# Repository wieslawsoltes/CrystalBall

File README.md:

# CrystalBall

**Aether Orb — hardware, firmware, manufacturing engineering and a WebGPU digital studio.**

A tabletop AI-assisted entertainment prop with a hollow optical globe, an operator-facing reflected display, push-to-talk audio and a decorative illuminated base. The browser recreates the concept's sphere, purple illumination, black/gold celestial base and private teller display; the Engineering view loads the actual CAD tessellation.

**Release: engineering candidate. Not approved for production manufacture or sale.** Physical fit, optical privacy/readability, supplier selection, thermal/electrical qualification, production security and market compliance remain release gates. The browser's volumetric nebula is artistic, not a claim that LEDs create a cloud inside an empty globe. Exact visual identity has not been accepted.

## Browser prototype online

**[Open CrystalBall on GitHub Pages](https://wieslawsoltes.github.io/CrystalBall/)** — offline demo by default, including the WebGPU experience and CAD inspector. The Python gateway is hosted separately. [Pages deployment and pairing](docs/github-pages.md) explains the repository-path checks, publication manifest and CORS configuration.

## Rendering and input hardening

The renderer now caps surface area and adapter dimensions, allows only one outstanding GPU frame, suspends redundant paused/CAD submissions, and adapts resolution with hysteresis. Device loss/disposal releases GPU resources and aborts stale initialization or CAD uploads. Two-finger pinch, focused-canvas arrow keys, +/- zoom and Home reset complement mouse controls. See [resource ownership and validation](docs/renderer-lifecycle.md). These are bounded-work/resource improvements, not measured hardware FPS claims.

## Start the browser without an API key

```sh
git clone https://github.com/wieslawsoltes/CrystalBall.git
cd CrystalBall
python -m http.server 8088 --directory web
```

Open `http://localhost:8088`. No build or CDN dependencies are needed. Demo readings are explicitly fictional samples. WebGPU is preferred; Canvas 2D is a fallback. The application includes teller/client/comparison modes, orbit/zoom, a separate glow-only client window, a CAD part inspector with explosion/isolation, text paging, cancellation and timed erasure. The client display mode is a presentation feature, not an authentication boundary.

## Use your OpenAI key for text and voice

The project API key stays on your trusted gateway host. The browser receives a separate device token; it does not ask for or persist an OpenAI project key.

```sh
python factory/configure_gateway.py --unit orb-0001 --url https://orb-gateway.home.arpa --speech
cd gateway
docker compose up --build -d
```

The tool prompts for the project key without echo and creates `gateway/.env` plus `factory/private/orb-0001.json` with restrictive POSIX permissions. It refuses to overwrite existing credentials. Windows deployments need corresponding NTFS ACLs.

Configure LAN DNS to point `orb-gateway.home.arpa` at the gateway machine. The supplied Caddy configuration uses a local CA: export and explicitly trust its **public root certificate** on your clients. Do not disable certificate verification or distribute CA private keys. Open the HTTPS site, select **Connect gateway**, enter its origin and the device token from the private JSON, then ask a question or hold the microphone button.

Text generation, transcription and synthesized speech use paid OpenAI APIs. Set model names in `.env` for models available to your account. No live paid provider test has been performed in this repository's CI. Speech requires `--speech`; the voice is disclosed as AI-generated. Experimental native WebRTC voice additionally requires `--realtime`. Leave it disabled for production until live provider/device and fault-injection qualification is completed. Known calls now have durable SQLite lifecycle recovery; ambiguous creates block new voice admission until an operator reconciles them. See [recovery and cancellation design](docs/runtime-recovery.md).

The gateway runs as UID 10001 on a read-only root filesystem, uses a persistent SQLite request-admission database, enforces bounded requests and permits a single worker. Request quotas are not exact monetary caps. The browser unlocks Web Audio in the user gesture, stops microphone tracks on cancellation and uses no local/session storage for credentials or transcripts. Actual Safari/iPhone audio and microphone behavior still require representative-device testing.

## Engineering and manufacturing files

| Area | Entry point |
|---|---|
| Manufacturing handbook | [Editable guide](manufacturing/handbook.md) / [PDF](manufacturing/generated/CrystalBall-RevB-Handbook.pdf) / [HTML](manufacturing/generated/handbook.html) |
| BOM, harness, inspection and fixture tables | [Generated manufacturing package](manufacturing/generated/) |
| Native KiCad CAM | [cam-native](manufacturing/cam-native/) — read the hold notice; do not mix export sets |
| ECAD project | [KiCad project](hardware/aether-carrier.kicad_pro), [PCB](hardware/aether-carrier.kicad_pcb), [schematic](hardware/aether-carrier.kicad_sch) |
| Mechanical source | [CadQuery generator](mechanical/model.py), [Rev B assembly STEP](mechanical/Aether_Orb_RevB_Assembly.step), individual [STEP](mechanical/step/) and [STL](mechanical/stl/) |
| Firmware | [ESP-IDF project](firmware/) |
| Gateway and browser | [gateway](gateway/) / [web](web/) |
| Commissioning | [Factory tools](factory/) |
| Release evidence gate | [Requirements](manufacturing/release-plan.json) / [checker](factory/release_gate.py) / [signed evidence](factory/evidence.py) |
| First-article data evaluator | [Draft plan](manufacturing/qualification-plan.json) / [measurement tool](factory/measurements.py) |
| Test provenance | [Verification notes](verification/README.md) and [validated screenshots](preview/validated/) |

The original **63 Rev A files** are preserved byte-for-byte at commit `f430900c5269cbada520c0550a1a0a9df75eb3ed`, checked by `provenance/reva/SHA256.json`. Subsequent revisions are separate commits. `parameters.json` is generated documentation; edit the mechanical generator's `P` dictionary, not that JSON, to change geometry.

## Build firmware and provision a development unit

Use ESP-IDF **v5.5.2** with the specified ESP32-S3-DevKitC-1-N8R8. Copy only your gateway's trusted public CA certificate to `firmware/main/gateway_ca.pem` and then:

```sh
cd firmware
idf.py set-target esp32s3
idf.py build
```

Before connecting DevKit USB: remove product power, allow and verify discharge, then **remove the DevKit from both carrier sockets**. Removing the RUN shunt alone does not isolate signal paths. Do not dual-power an installed DevKit.

```sh
# From repository root, in an activated ESP-IDF environment:
python factory/provision.py --device factory/private/orb-0001.json --generate
# Explicit NVS-only flash, with the DevKit already removed from both sockets:
python factory/provision.py --device factory/private/orb-0001.json --flash --port /dev/ttyUSB0 --devkit-detached
```

Use one provisioning invocation for a unit: the tool deliberately refuses to reuse its private output folder. The passphrase is prompted without echo. NVS offsets come from the checked-in partition table. **This is plaintext development provisioning, not production secure storage.** No eFuses are automatically changed. Production signing/encryption, key custody, recovery and update policy require an approved security workflow. The three network-capable CI profiles use disposable build-only CAs and are not deployable customer firmware. The separate offline diagnostic artifact below needs no CA, but remains bench-only and physically unqualified.

## Offline first-article diagnostics

The fourth firmware profile, **factory-diagnostics**, has a separate entry point and does not initialize application networking or read device credentials. It provides ten button-driven pages: instructions, optical alignment grid, black, white, RGB bars, checkerboard, gray ramp, a 16-pixel RGB walk, a held-button 1 kHz test tone and microphone digital statistics. Capture is not saved or uploaded. Driver success and digital levels never become automatic manufacturing passes.

Read [the complete bench procedure](docs/bench-diagnostics.md) before using the diagnostic build. The same detached-DevKit programming rule applies. From an activated ESP-IDF 5.5.2 environment, in `firmware/`:

```sh
idf.py -B build-diagnostics \
  -D SDKCONFIG="$PWD/build-diagnostics/sdkconfig" \
  -D SDKCONFIG_DEFAULTS="sdkconfig.defaults;sdkconfig.diagnostics" \
  -D IDF_TARGET=esp32s3 build
```

CI inspects the linked diagnostic image and exact flash-image addresses before producing **factory-diagnostics-bench-only-NOT-CUSTOMER-FIRMWARE**. That artifact contains only the bootloader, partition table, diagnostic application, flashing metadata and a source/hash manifest. No NVS provisioning image, gateway CA or credential is included. Do not flash it to a security-enrolled production controller or mistake it for an approved customer release.

## Verify and regenerate

```sh
python -m pip install './gateway[test]' reportlab
python -m pytest gateway/tests factory/tests -q
npm --prefix web test
python tools/manufacturing.py
python factory/release_gate.py --output manufacturing/generated/release-status.json
```

The final command currently exits **1 / BLOCKED** because physical qualification and owner approvals are absent. That is intentional. Without a trust policy it validates structure only. With an independently pinned reviewer policy, it verifies Ed25519 signatures, scoped reviewer quorums, expiry/revocation and both source and manufacturing-output fingerprints. No trusted reviewer ships with the project. Neither mode certifies the product or authorizes production. See [signed evidence and measured qualification](docs/qualification-evidence.md).

GitHub Actions also compiles all four firmware profiles, runs KiCad 9.0.9 ERC/DRC/schematic parity, exports native CAM, tests a read-only Docker deployment and exercises the browser on a software WebGPU adapter with mocked OpenAI responses. See [Actions](https://github.com/wieslawsoltes/CrystalBall/actions) for the exact commit under test. Archived evidence is dated, not automatically promoted to cover later design changes.

The [bench/renderer batch record](verification/bench-renderer/summary.json) links the exact engineering, browser and public Pages runs and distinguishes their source commits. It is an engineering evidence index, not a signed release authorization.

## Remaining production gates

The handbook and generated tables distinguish selected ordering codes from unresolved suppliers, proposed assembly lengths/torques/acceptance limits from measured limits, and envelope models from real components. Optical viewing-volume tests, a fitted first article, power/inrush/fault/thermal tests, radio/EMC/ESD and market assessment, secure provisioning/recovery, real OpenAI/mobile-device validation, assembly capability and transport qualification are still required. No conformity mark or production authorization is implied by this repository.

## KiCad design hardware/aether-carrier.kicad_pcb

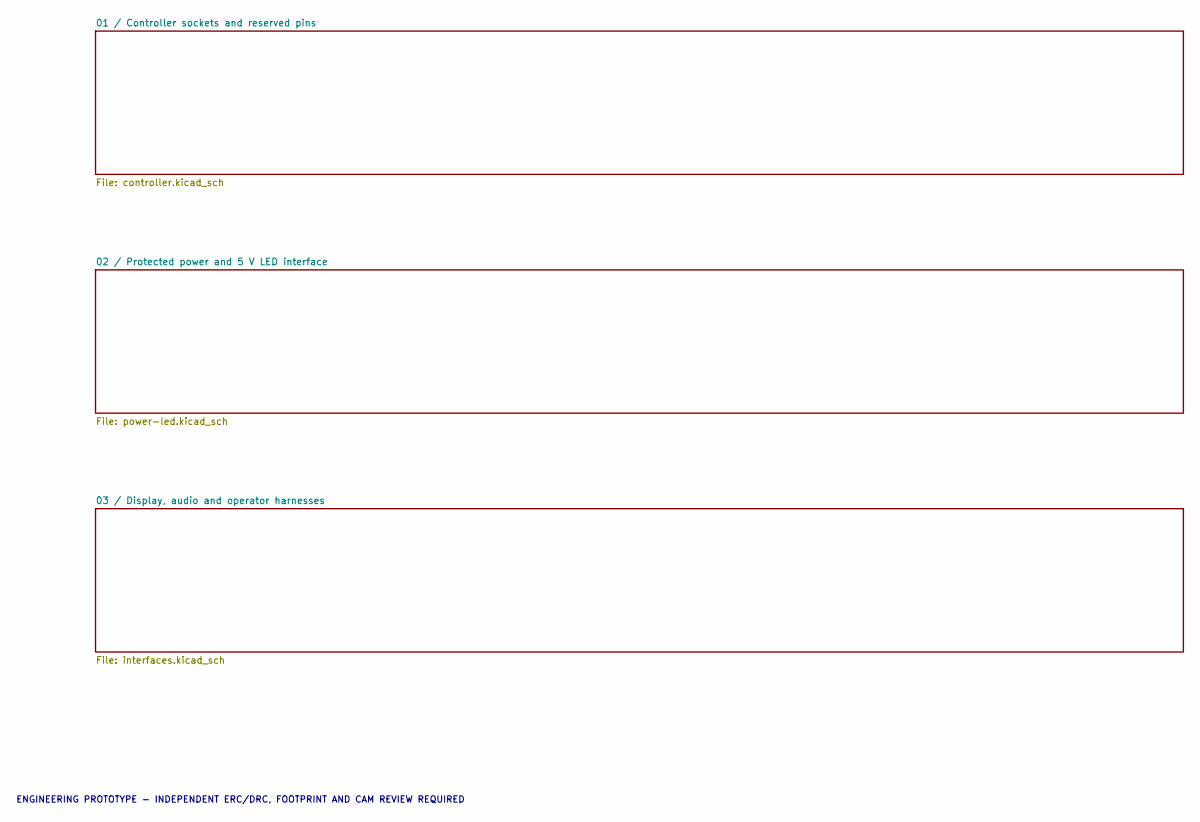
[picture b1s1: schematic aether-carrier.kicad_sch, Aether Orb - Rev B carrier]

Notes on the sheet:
ENGINEERING PROTOTYPE - INDEPENDENT ERC/DRC, FOOTPRINT AND CAM REVIEW REQUIRED

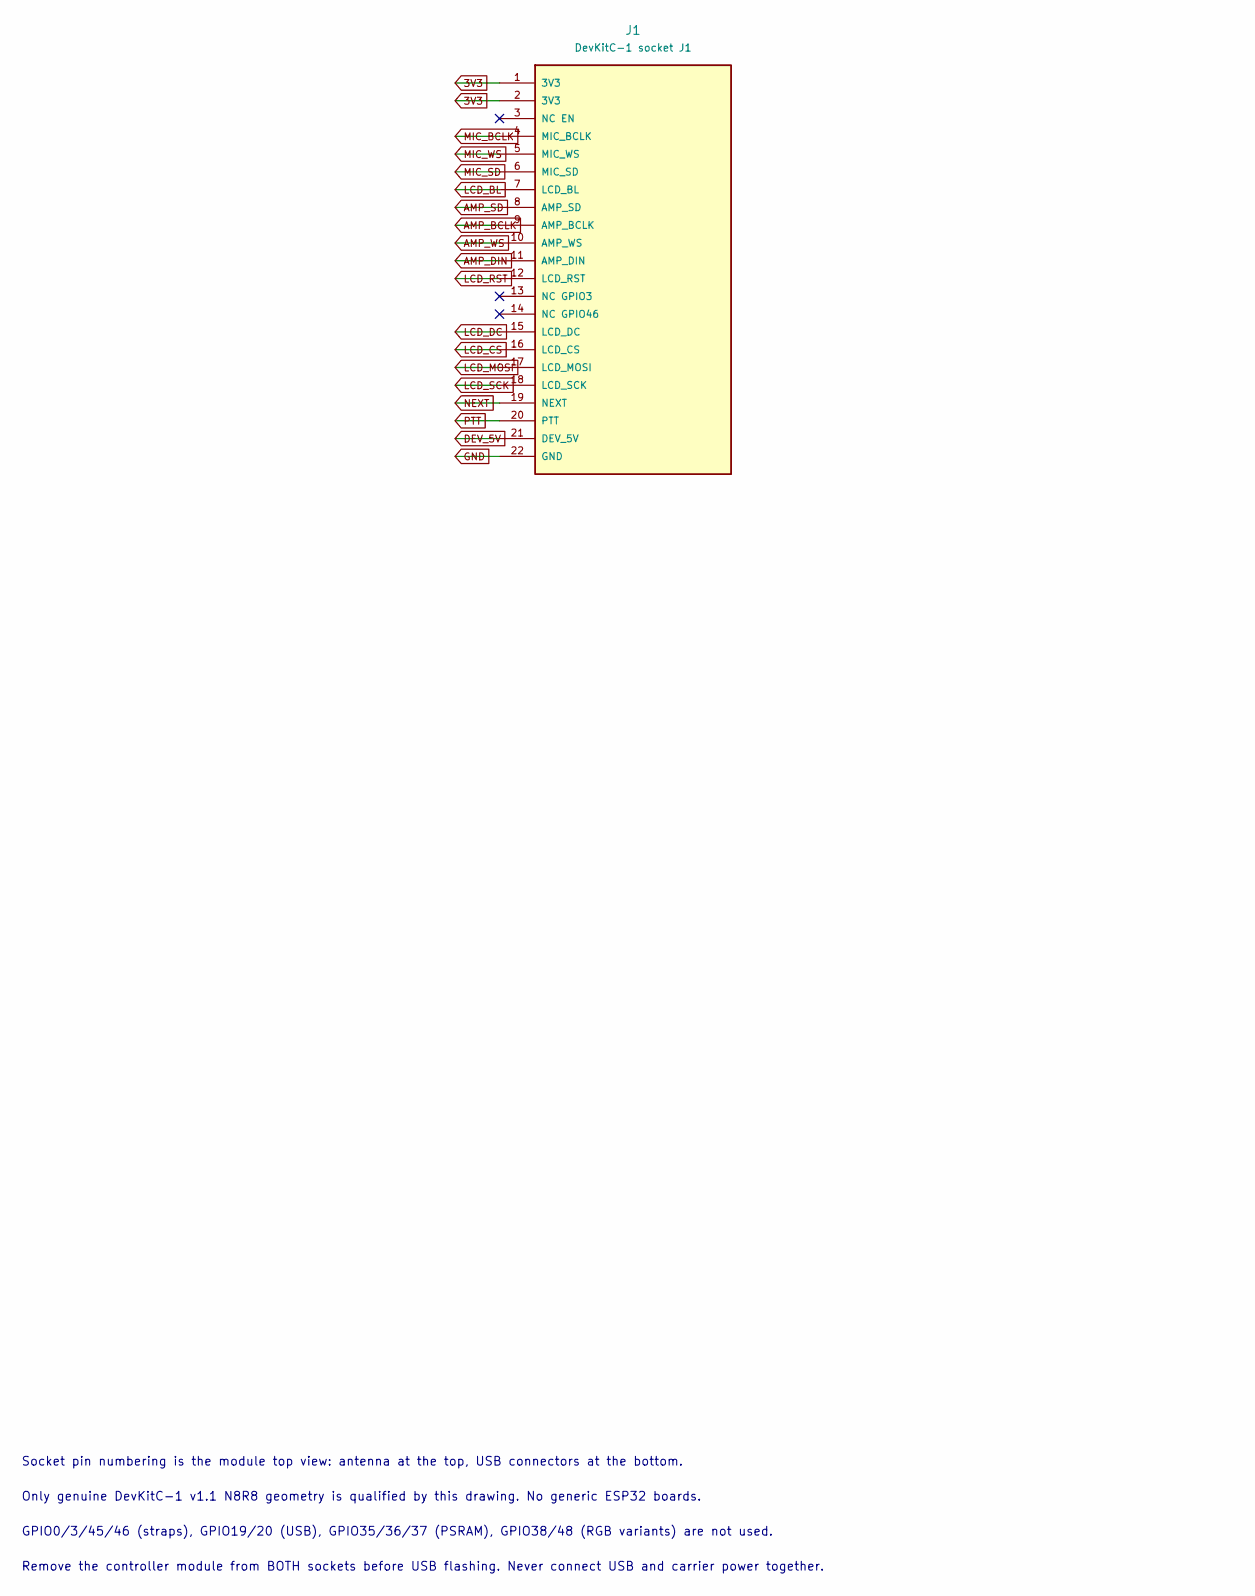
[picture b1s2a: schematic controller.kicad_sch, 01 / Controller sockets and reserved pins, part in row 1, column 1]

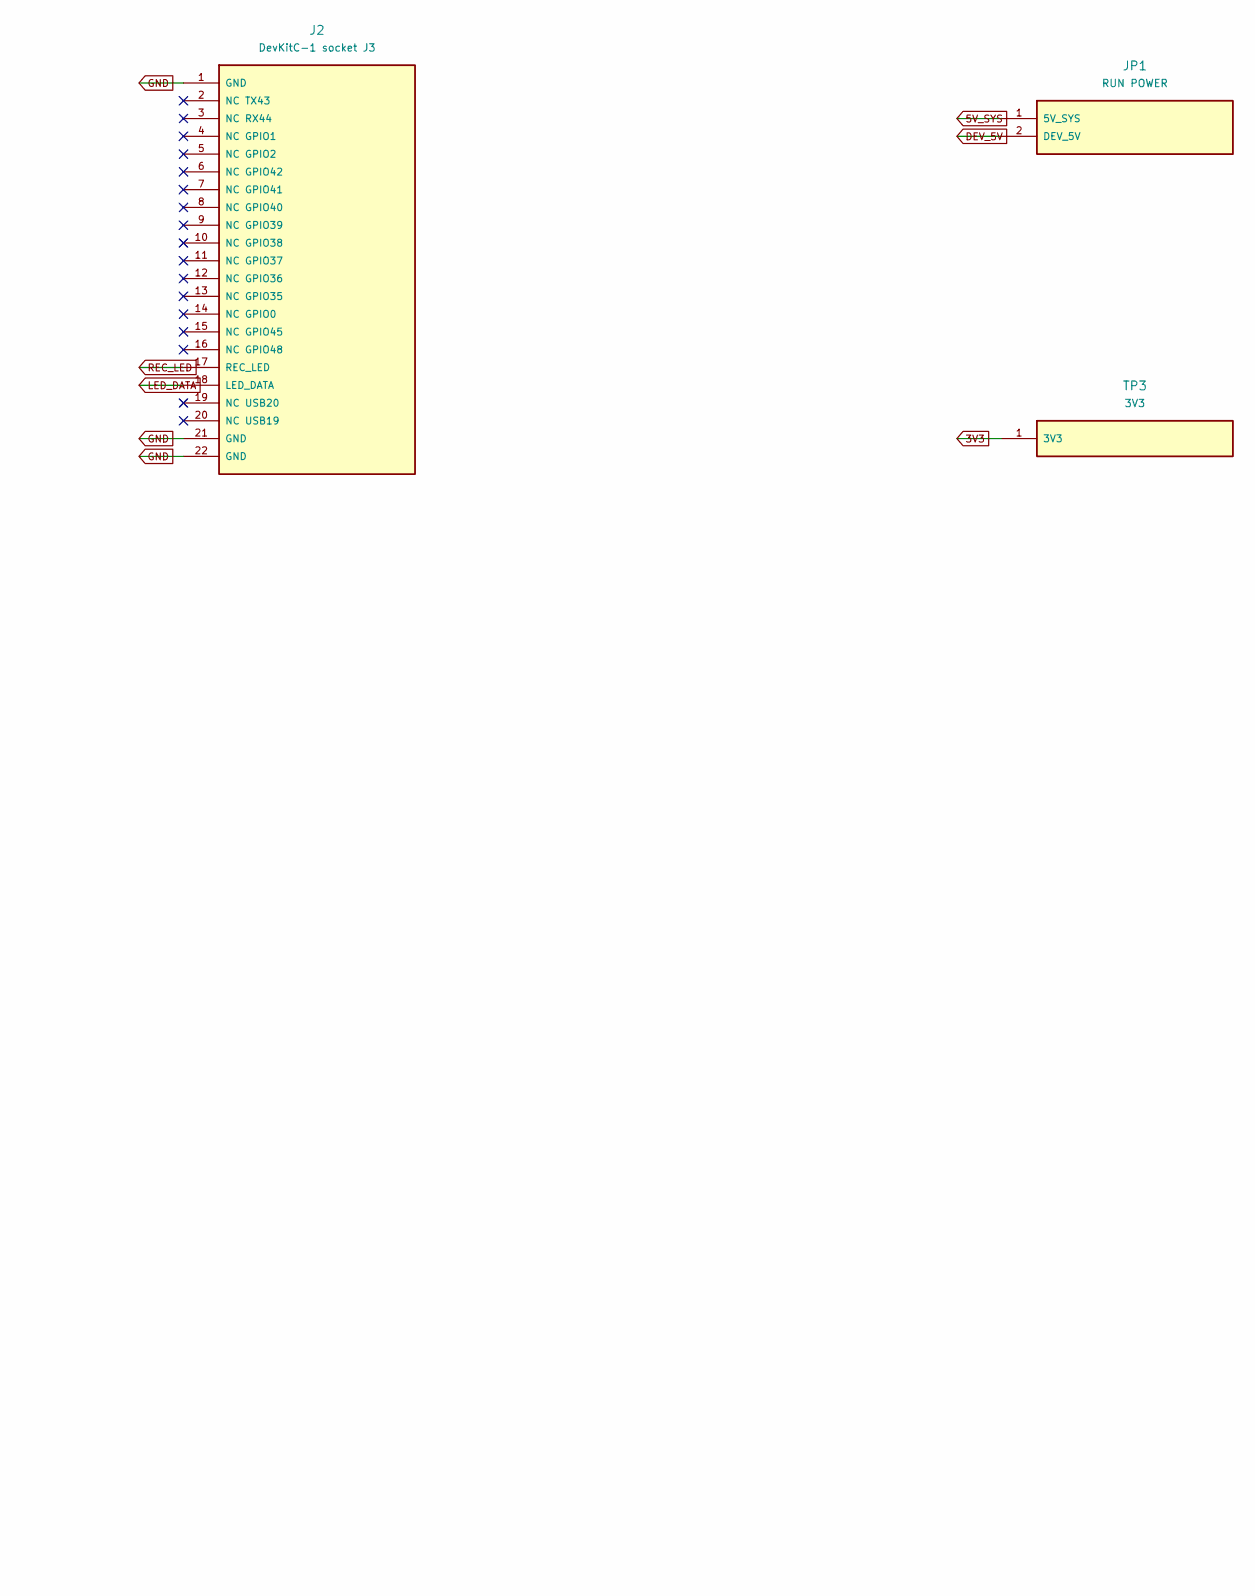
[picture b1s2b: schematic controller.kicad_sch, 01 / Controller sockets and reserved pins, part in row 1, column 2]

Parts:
J1: DevKitC-1 socket J1; Socket_1x22_P2.54_J1
J2: DevKitC-1 socket J3; Socket_1x22_P2.54_J2
JP1: RUN POWER; PinHeader_1x02_P2.54_JP1
TP3: 3V3; TestPoint_THT_D2_TP3

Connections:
3V3: J1.1 (3V3), J1.2 (3V3), TP3.1; also elsewhere on the board
5V_SYS: JP1.1 (5V_SYS); also elsewhere on the board
AMP_BCLK: J1.9 (AMP_BCLK); also elsewhere on the board
AMP_DIN: J1.11 (AMP_DIN); also elsewhere on the board
AMP_SD: J1.8 (AMP_SD); also elsewhere on the board
AMP_WS: J1.10 (AMP_WS); also elsewhere on the board
DEV_5V: J1.21 (DEV_5V), JP1.2 (DEV_5V)
GND: J1.22 (GND), J2.1 (GND), J2.21 (GND), J2.22 (GND); also elsewhere on the board
LCD_BL: J1.7 (LCD_BL); also elsewhere on the board
LCD_CS: J1.16 (LCD_CS); also elsewhere on the board
LCD_DC: J1.15 (LCD_DC); also elsewhere on the board
LCD_MOSI: J1.17 (LCD_MOSI); also elsewhere on the board
LCD_RST: J1.12 (LCD_RST); also elsewhere on the board
LCD_SCK: J1.18 (LCD_SCK); also elsewhere on the board
LED_DATA: J2.18 (LED_DATA); also elsewhere on the board
MIC_BCLK: J1.4 (MIC_BCLK); also elsewhere on the board
MIC_SD: J1.6 (MIC_SD); also elsewhere on the board
MIC_WS: J1.5 (MIC_WS); also elsewhere on the board
NEXT: J1.19 (NEXT); also elsewhere on the board
PTT: J1.20 (PTT); also elsewhere on the board
REC_LED: J2.17 (REC_LED); also elsewhere on the board

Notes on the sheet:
Socket pin numbering is the module top view: antenna at the top, USB connectors at the bottom.
Only genuine DevKitC-1 v1.1 N8R8 geometry is qualified by this drawing. No generic ESP32 boards.
GPIO0/3/45/46 (straps), GPIO19/20 (USB), GPIO35/36/37 (PSRAM), GPIO38/48 (RGB variants) are not used.
Remove the controller module from BOTH sockets before USB flashing. Never connect USB and carrier power together.

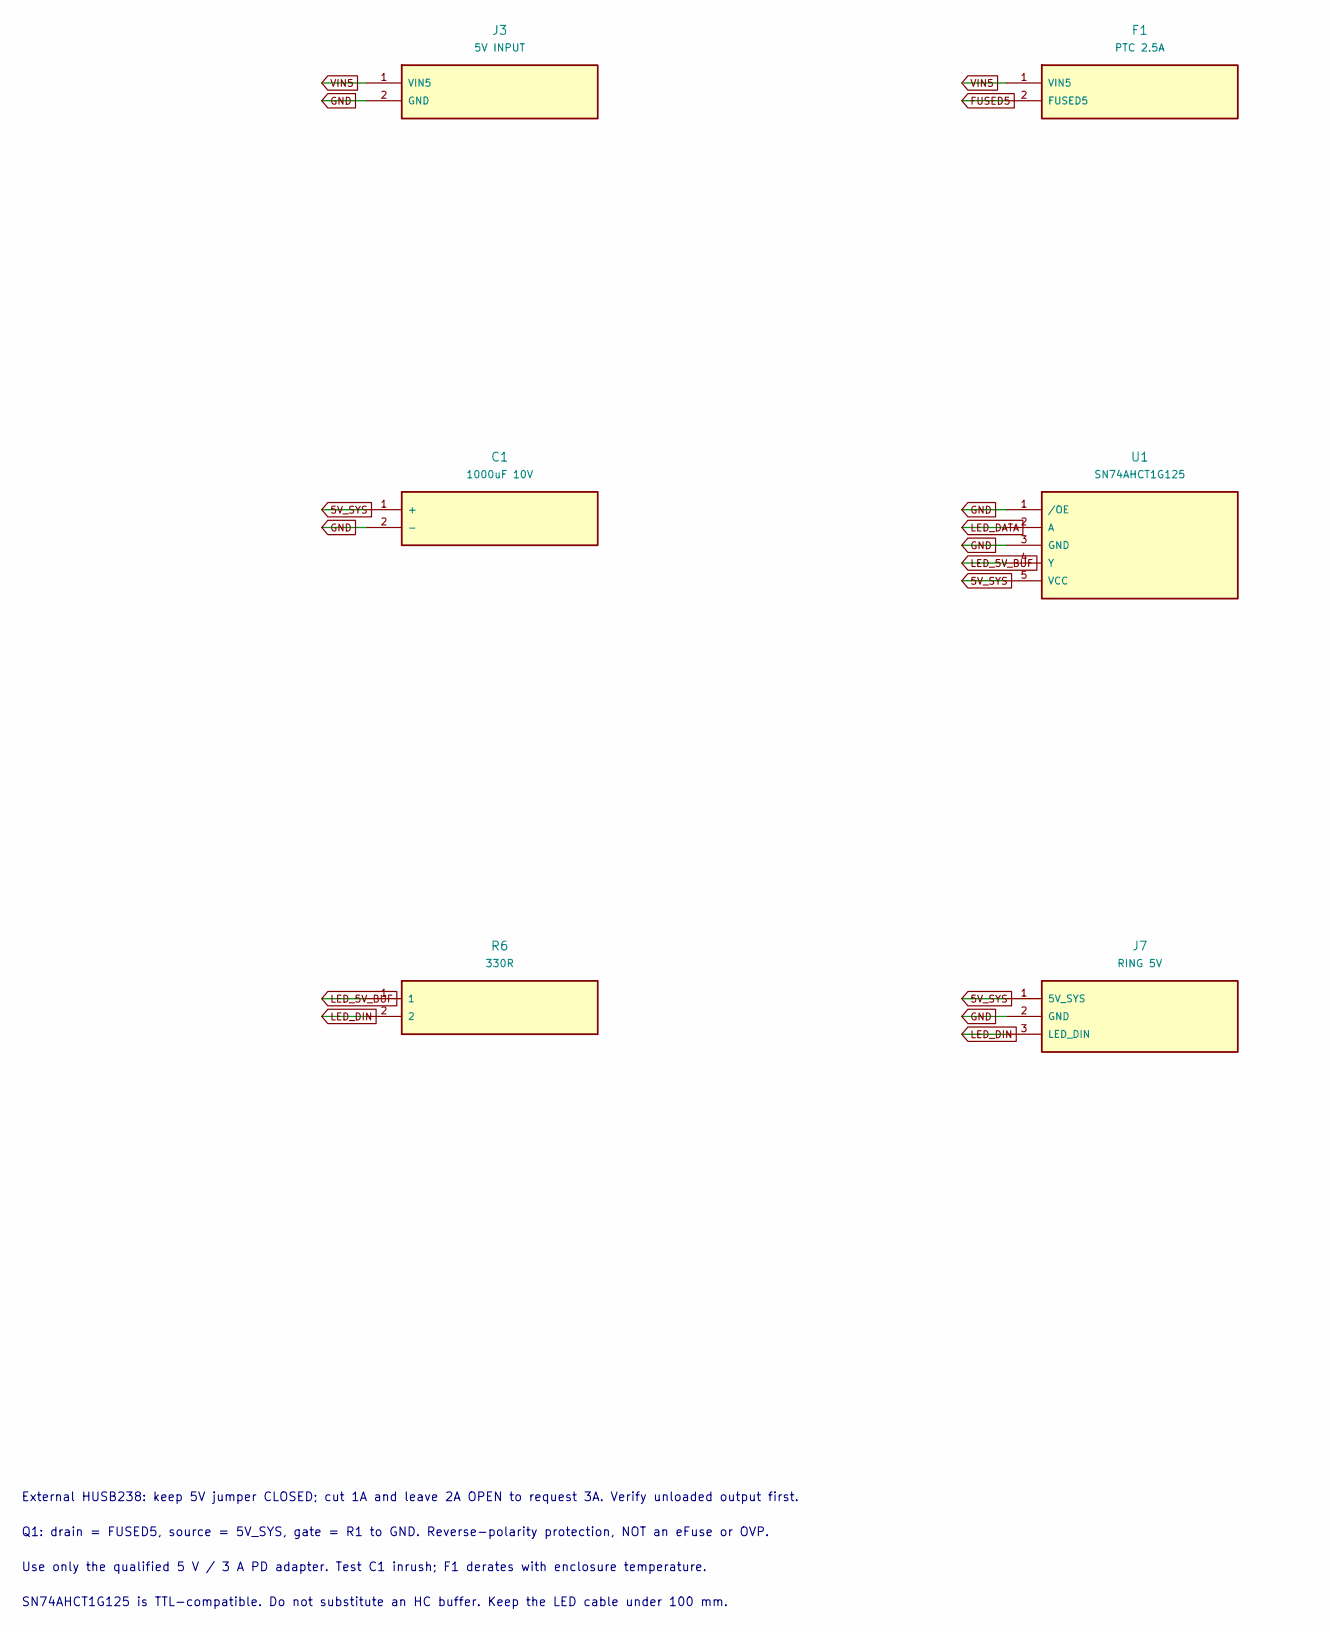
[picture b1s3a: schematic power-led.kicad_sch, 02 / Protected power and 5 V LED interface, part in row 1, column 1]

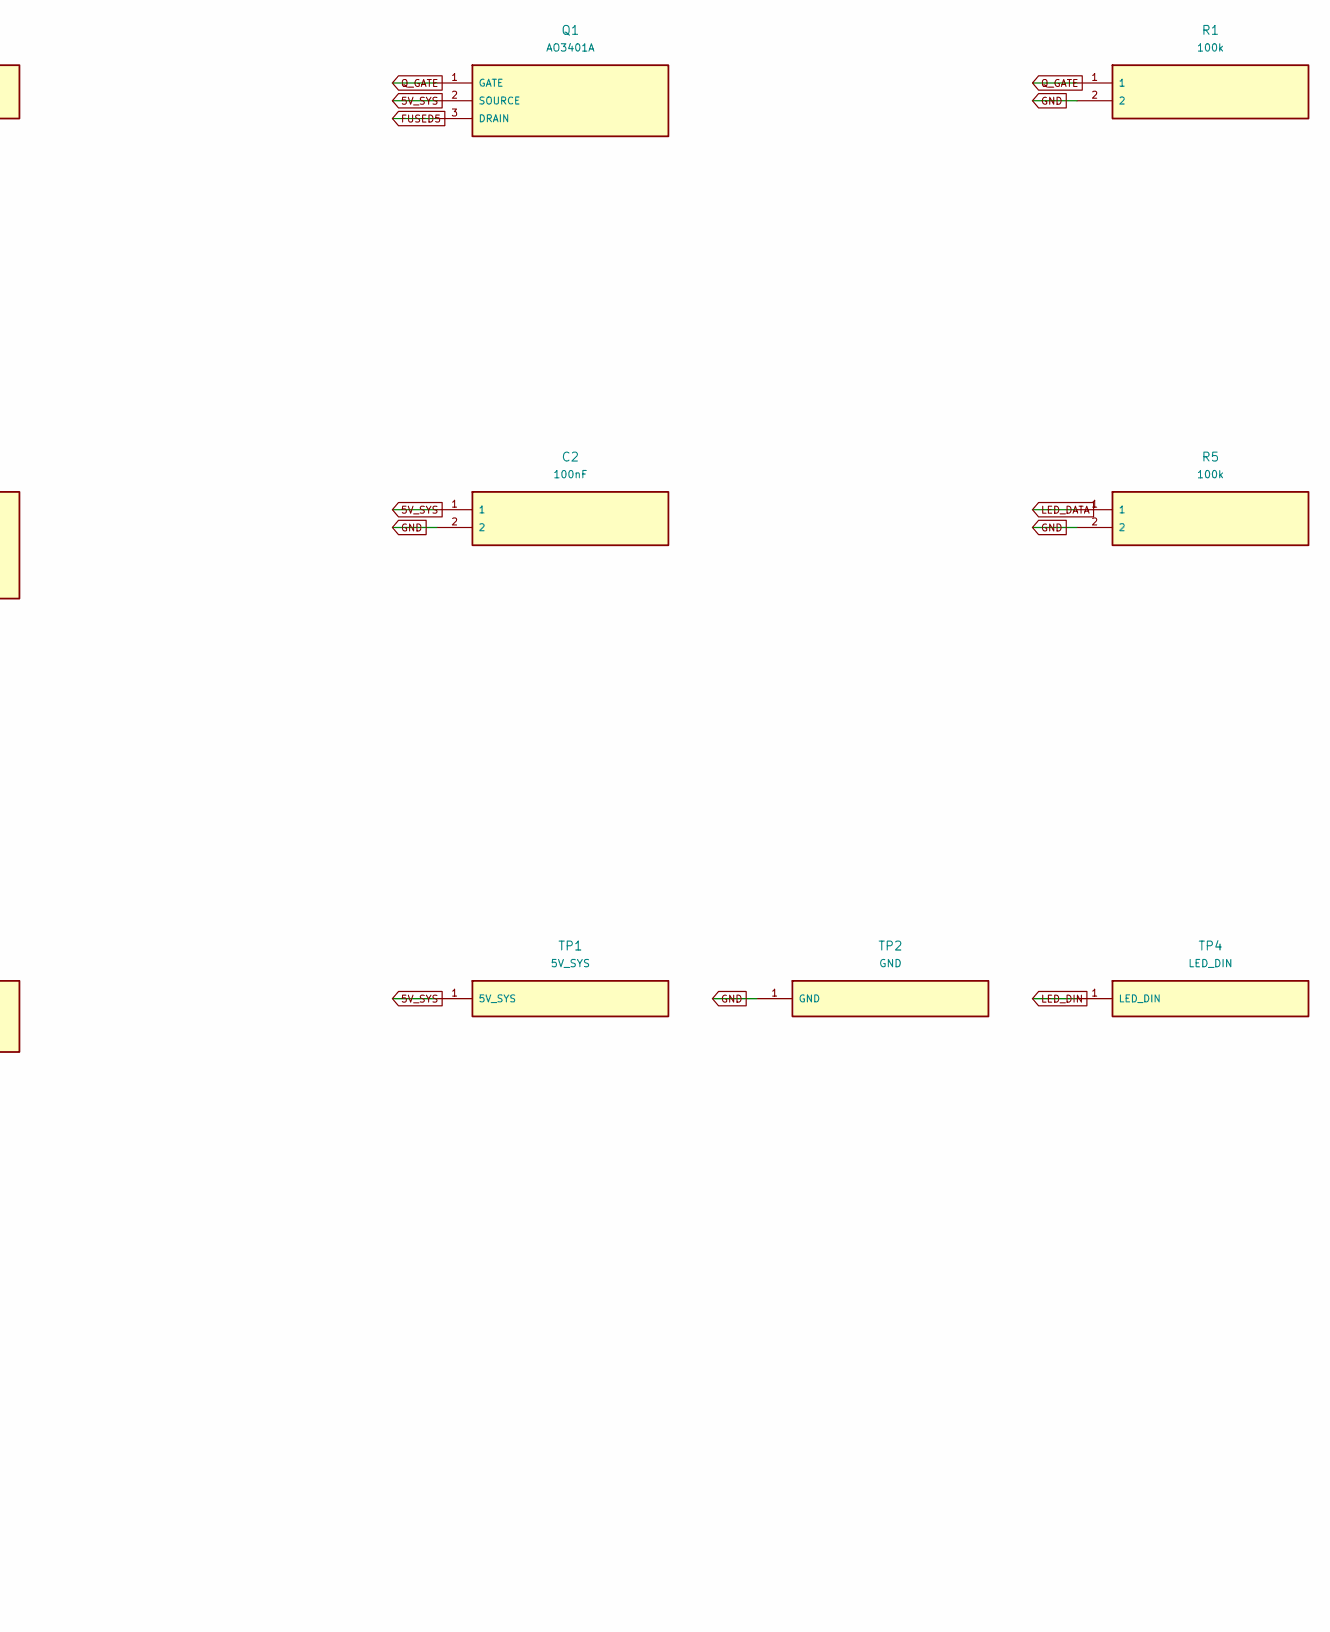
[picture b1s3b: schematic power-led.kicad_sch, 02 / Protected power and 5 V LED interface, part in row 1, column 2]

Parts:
C1: 1000uF 10V; CP_Radial_D10_P5_C1
C2: 100nF; C_0805_2012Metric_C2
F1: PTC 2.5A; PTC_P5.08_F1
J3: 5V INPUT; Terminal_1x02_P5.08_J3
J7: RING 5V; XH_1x03_P2.50_J7
Q1: AO3401A; SOT-23_Q1
R1: 100k; R_0805_2012Metric_R1
R5: 100k; R_0805_2012Metric_R5
R6: 330R; R_0805_2012Metric_R6
TP1: 5V_SYS; TestPoint_THT_D2_TP1
TP2: GND; TestPoint_THT_D2_TP2
TP4: LED_DIN; TestPoint_THT_D2_TP4
U1: SN74AHCT1G125; SOT-23-5_U1

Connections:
5V_SYS: C1.1 (+), C2.1, J7.1 (5V_SYS), Q1.2 (SOURCE), TP1.1, U1.5 (VCC); also elsewhere on the board
FUSED5: F1.2 (FUSED5), Q1.3 (DRAIN)
GND: C1.2 (-), C2.2, J3.2 (GND), J7.2 (GND), R1.2, R5.2, TP2.1, U1.1 (/OE), U1.3 (GND); also elsewhere on the board
LED_5V_BUF: R6.1, U1.4 (Y)
LED_DATA: R5.1, U1.2 (A); also elsewhere on the board
LED_DIN: J7.3 (LED_DIN), R6.2, TP4.1
Q_GATE: Q1.1 (GATE), R1.1
VIN5: F1.1 (VIN5), J3.1 (VIN5)

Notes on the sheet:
External HUSB238: keep 5V jumper CLOSED; cut 1A and leave 2A OPEN to request 3A. Verify unloaded output first.
Q1: drain = FUSED5, source = 5V_SYS, gate = R1 to GND. Reverse-polarity protection, NOT an eFuse or OVP.
Use only the qualified 5 V / 3 A PD adapter. Test C1 inrush; F1 derates with enclosure temperature.
SN74AHCT1G125 is TTL-compatible. Do not substitute an HC buffer. Keep the LED cable under 100 mm.

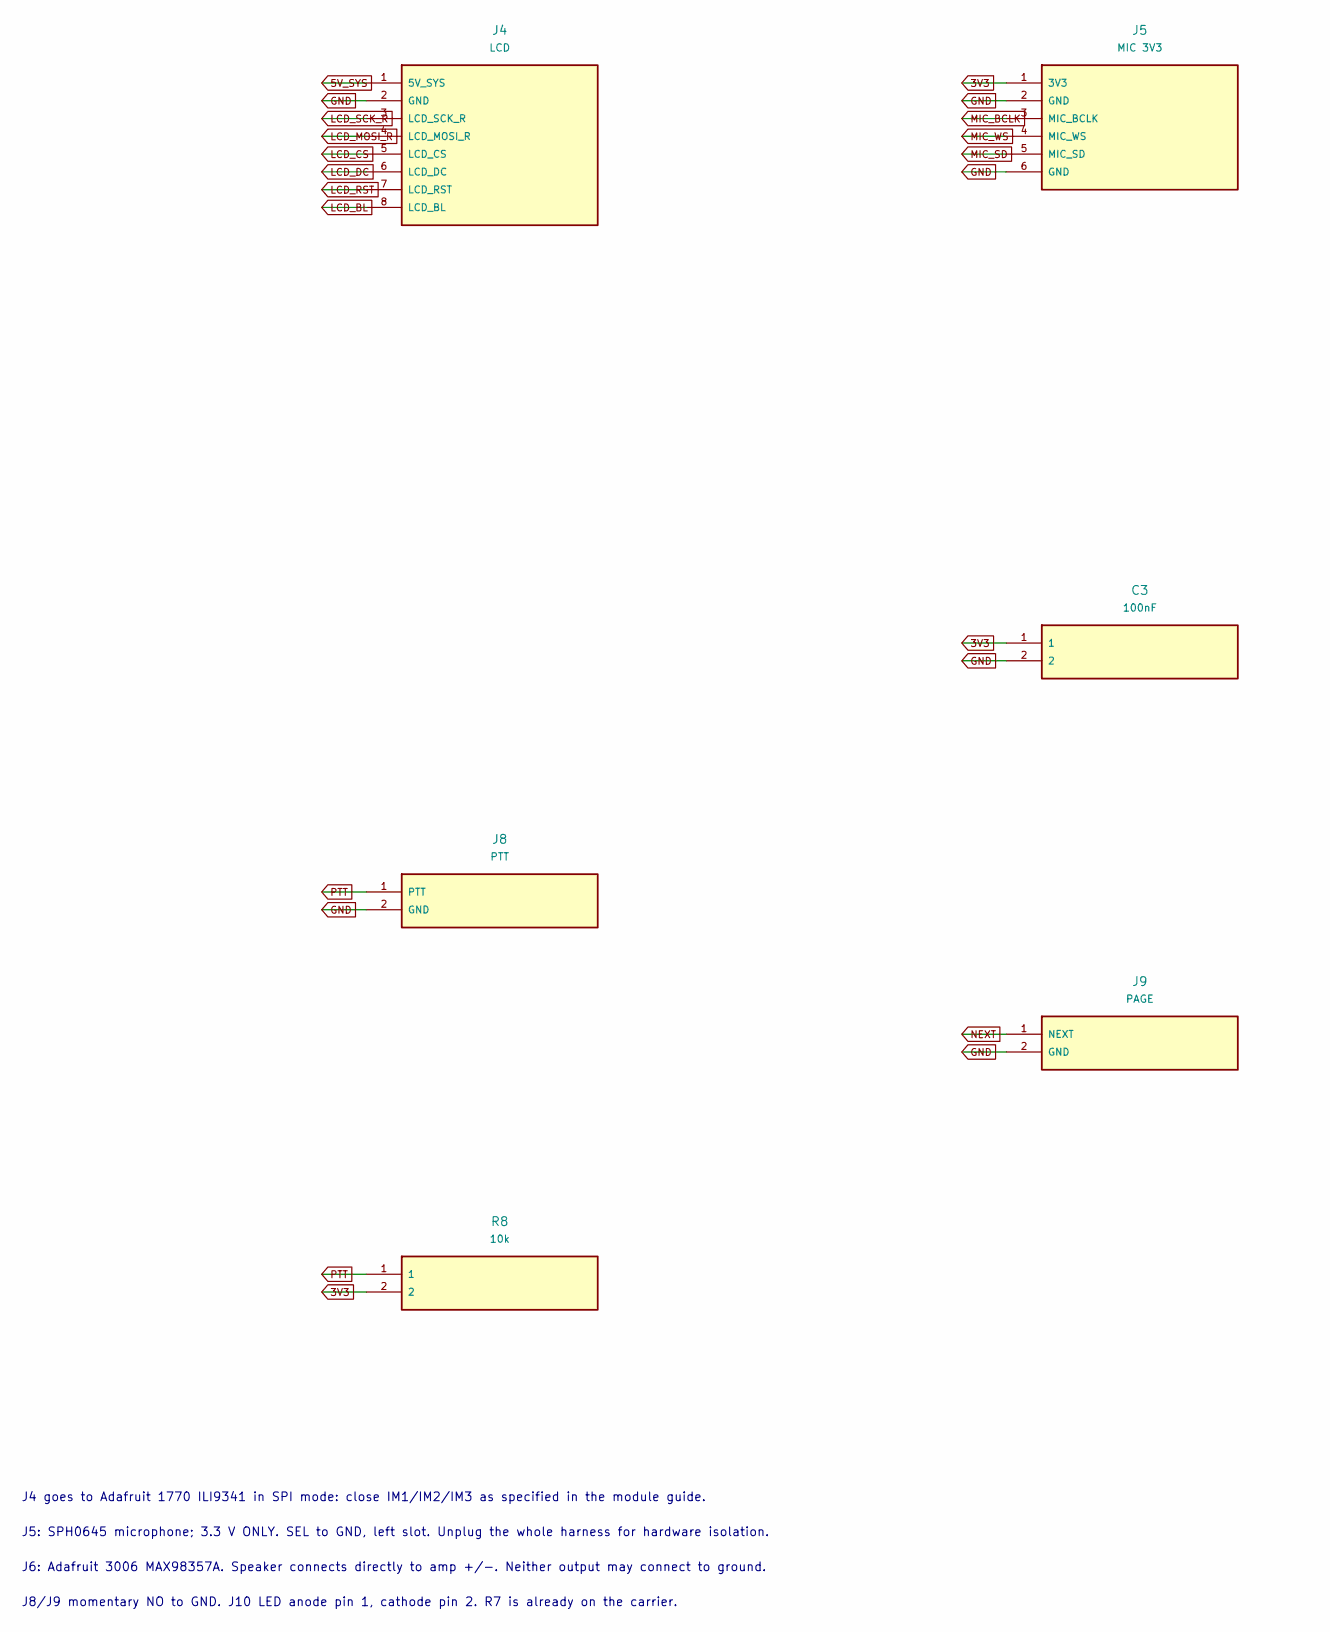
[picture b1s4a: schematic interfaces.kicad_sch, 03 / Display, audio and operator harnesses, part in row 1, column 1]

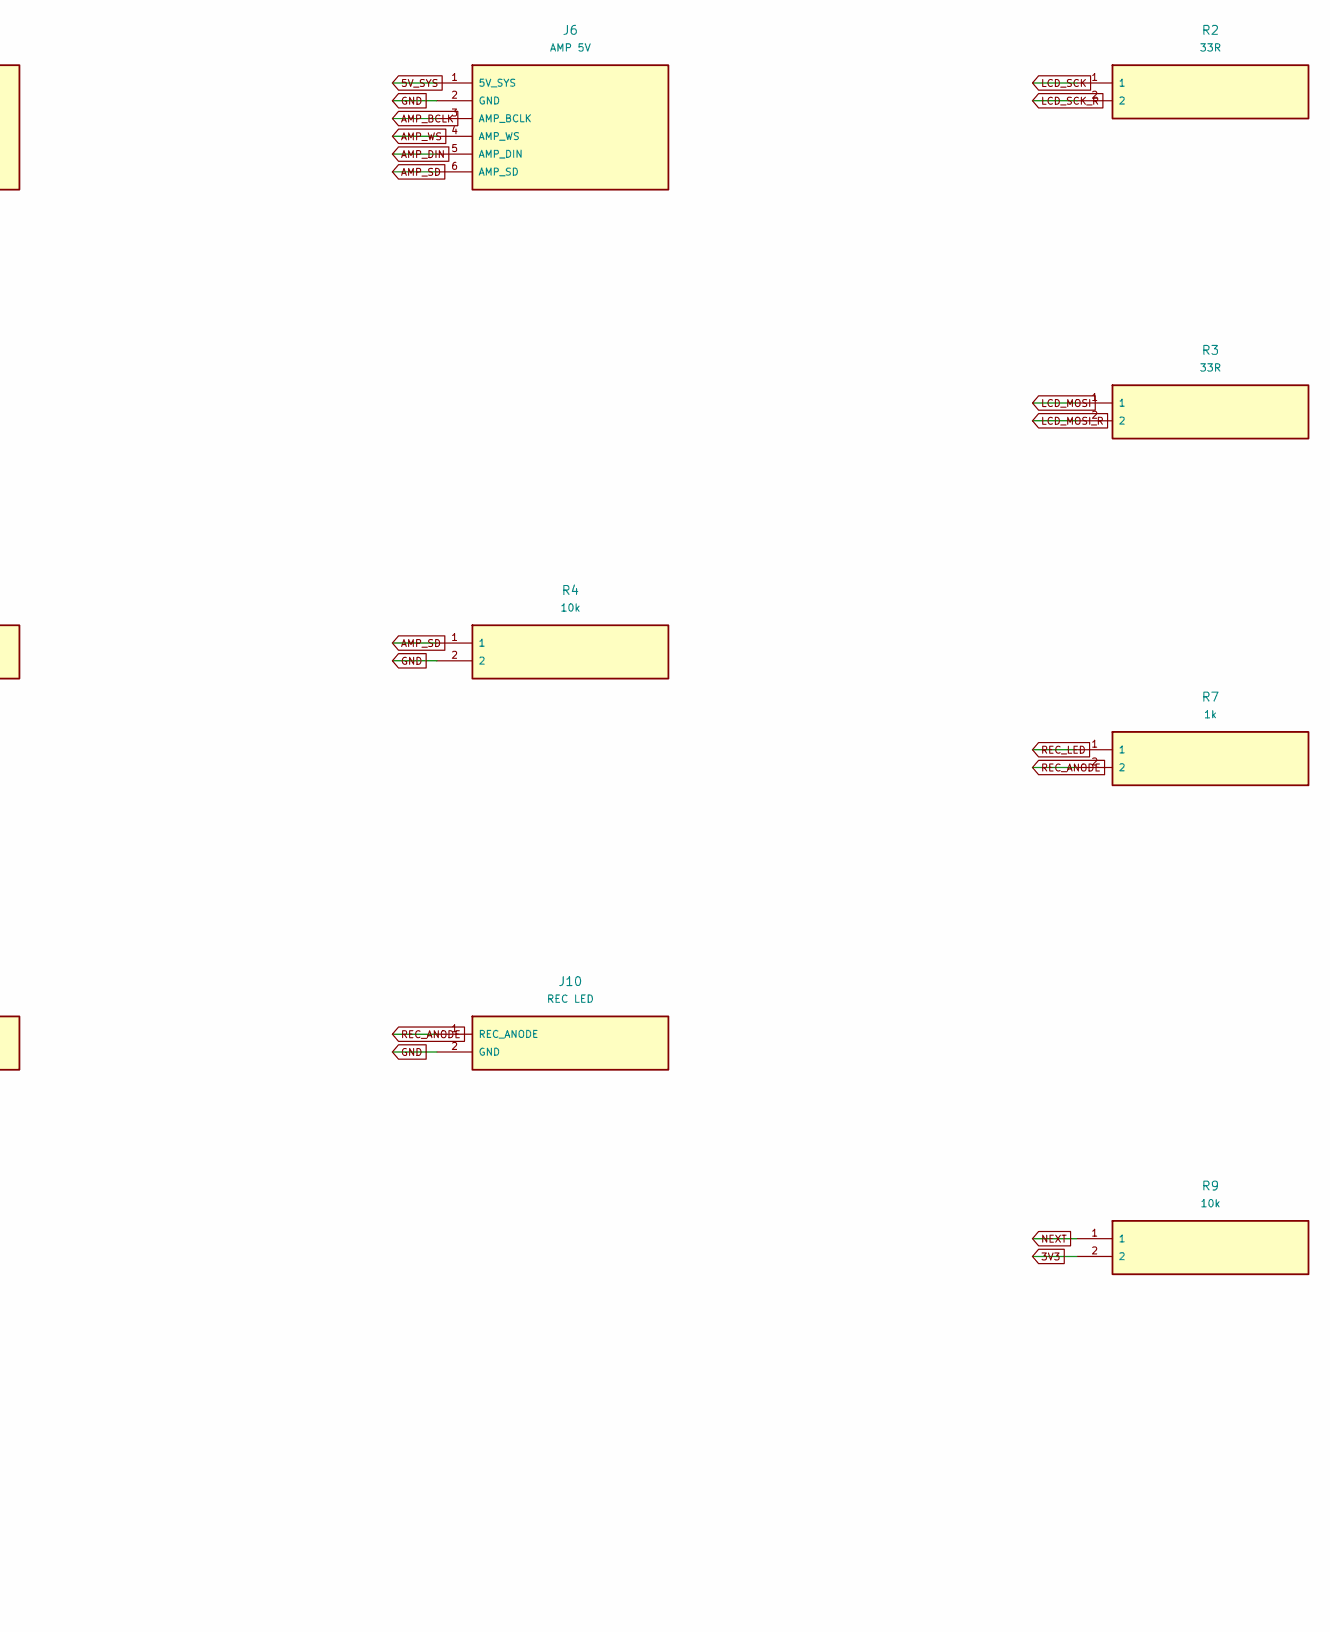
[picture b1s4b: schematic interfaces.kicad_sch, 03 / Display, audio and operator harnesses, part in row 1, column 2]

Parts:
C3: 100nF; C_0805_2012Metric_C3
J4: LCD; XH_1x08_P2.50_J4
J5: MIC 3V3; XH_1x06_P2.50_J5
J6: AMP 5V; XH_1x06_P2.50_J6
J8: PTT; XH_1x02_P2.50_J8
J9: PAGE; XH_1x02_P2.50_J9
J10: REC LED; XH_1x02_P2.50_J10
R2: 33R; R_0805_2012Metric_R2
R3: 33R; R_0805_2012Metric_R3
R4: 10k; R_0805_2012Metric_R4
R7: 1k; R_0805_2012Metric_R7
R8: 10k; R_0805_2012Metric_R8
R9: 10k; R_0805_2012Metric_R9

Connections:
3V3: C3.1, J5.1 (3V3), R8.2, R9.2; also elsewhere on the board
5V_SYS: J4.1 (5V_SYS), J6.1 (5V_SYS); also elsewhere on the board
AMP_BCLK: J6.3 (AMP_BCLK); also elsewhere on the board
AMP_DIN: J6.5 (AMP_DIN); also elsewhere on the board
AMP_SD: J6.6 (AMP_SD), R4.1; also elsewhere on the board
AMP_WS: J6.4 (AMP_WS); also elsewhere on the board
GND: C3.2, J4.2 (GND), J5.2 (GND), J5.6 (GND), J6.2 (GND), J8.2 (GND), J9.2 (GND), J10.2 (GND), R4.2; also elsewhere on the board
LCD_BL: J4.8 (LCD_BL); also elsewhere on the board
LCD_CS: J4.5 (LCD_CS); also elsewhere on the board
LCD_DC: J4.6 (LCD_DC); also elsewhere on the board
LCD_MOSI: R3.1; also elsewhere on the board
LCD_MOSI_R: J4.4 (LCD_MOSI_R), R3.2
LCD_RST: J4.7 (LCD_RST); also elsewhere on the board
LCD_SCK: R2.1; also elsewhere on the board
LCD_SCK_R: J4.3 (LCD_SCK_R), R2.2
MIC_BCLK: J5.3 (MIC_BCLK); also elsewhere on the board
MIC_SD: J5.5 (MIC_SD); also elsewhere on the board
MIC_WS: J5.4 (MIC_WS); also elsewhere on the board
NEXT: J9.1 (NEXT), R9.1; also elsewhere on the board
PTT: J8.1 (PTT), R8.1; also elsewhere on the board
REC_ANODE: J10.1 (REC_ANODE), R7.2
REC_LED: R7.1; also elsewhere on the board

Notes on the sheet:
J4 goes to Adafruit 1770 ILI9341 in SPI mode: close IM1/IM2/IM3 as specified in the module guide.
J5: SPH0645 microphone; 3.3 V ONLY. SEL to GND, left slot. Unplug the whole harness for hardware isolation.
J6: Adafruit 3006 MAX98357A. Speaker connects directly to amp +/-. Neither output may connect to ground.
J8/J9 momentary NO to GND. J10 LED anode pin 1, cathode pin 2. R7 is already on the carrier.
